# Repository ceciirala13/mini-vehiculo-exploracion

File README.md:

# mini-rover-lunar
Diseño prototipo de un mini rover lunar

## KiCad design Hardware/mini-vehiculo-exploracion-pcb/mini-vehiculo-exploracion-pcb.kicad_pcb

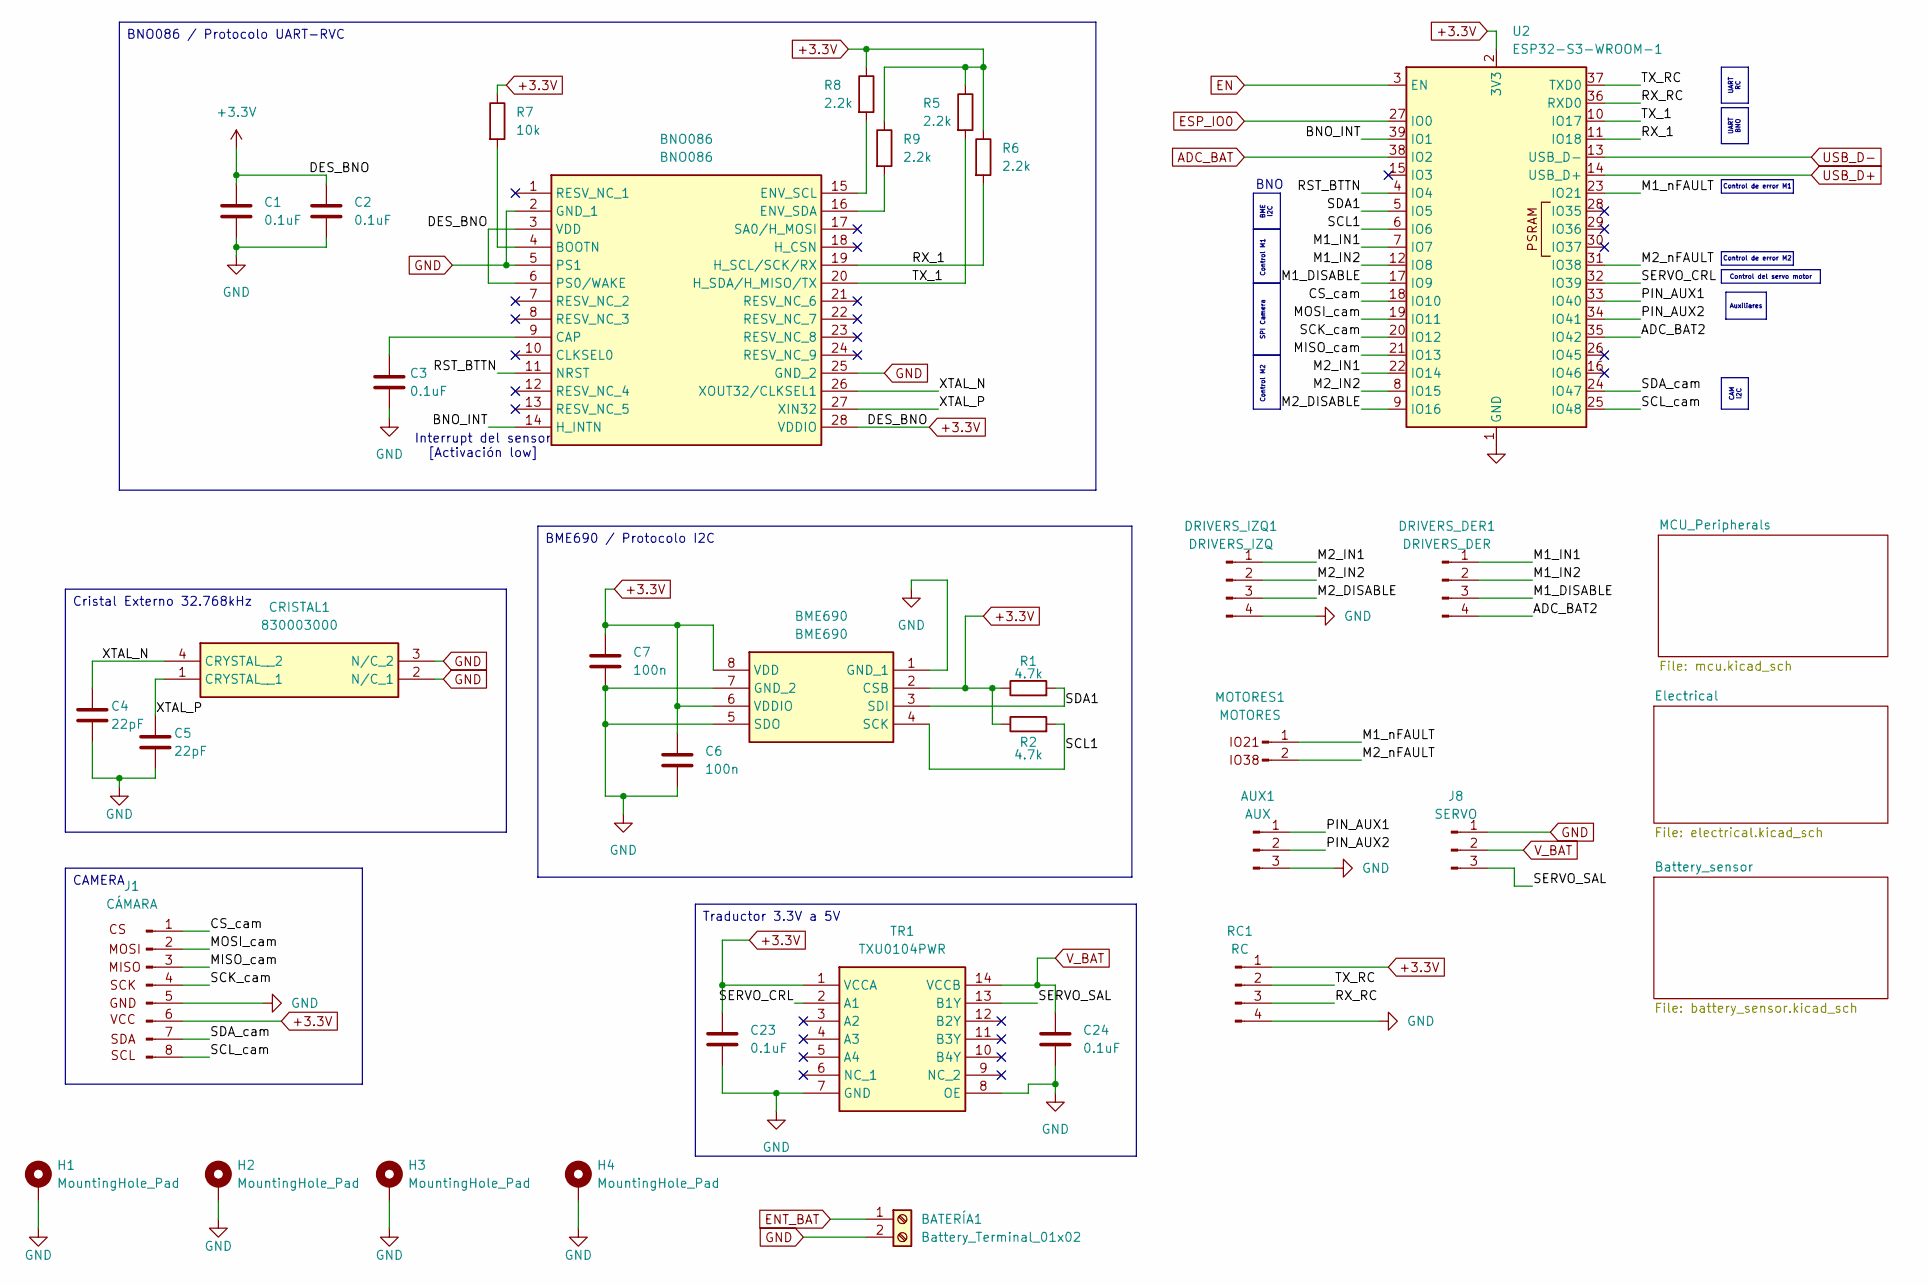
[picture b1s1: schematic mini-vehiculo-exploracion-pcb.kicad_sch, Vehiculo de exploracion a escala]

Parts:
AUX1: AUX; PinSocket_1x03_P2.54mm_Vertical
BATERÍA1: Battery_Terminal_01x02; TerminalBlock_Phoenix_MPT-0,5-2-2.54_1x02_P2.54mm_Horizontal
BME690: BME690; Mouser Part Number 262-BME690
BNO086: BNO086; Mouser Part Number 526-BNO086
C1, C2, C3, C23, C24: 0.1uF; C_0805_2012Metric_Pad1.18x1.45mm_HandSolder
C4, C5: 22pF; C_0805_2012Metric_Pad1.18x1.45mm_HandSolder
C6, C7: 100n; C_0805_2012Metric_Pad1.18x1.45mm_HandSolder
CRISTAL1: 830003000; Mouser Part Number 710-830003000
DRIVERS_DER1: DRIVERS_DER; PinSocket_1x04_P2.54mm_Vertical
DRIVERS_IZQ1: DRIVERS_IZQ; PinSocket_1x04_P2.54mm_Vertical
H1, H2, H3, H4: MountingHole_Pad; MountingHole_3.2mm_M3_Pad_Via
J1: CÁMARA; ArducamMINIOV2640
J8: SERVO; PinSocket_1x03_P2.54mm_Vertical
MOTORES1: MOTORES; PinSocket_1x02_P2.54mm_Vertical
R1, R2: 4.7k; R_0805_2012Metric_Pad1.20x1.40mm_HandSolder
R5, R6, R8, R9: 2.2k; R_0805_2012Metric_Pad1.20x1.40mm_HandSolder
R7: 10k; R_0805_2012Metric_Pad1.20x1.40mm_HandSolder
RC1: RC; PinSocket_1x04_P2.54mm_Vertical
TR1: TXU0104PWR; SOP65P640X120-14N; Mouser Part Number 595-TXU0104PWR
U2: ESP32-S3-WROOM-1; ESP32-S3-WROOM-1-P3JLC

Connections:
+3.3V: BME690.2 (CSB), BME690.6 (VDDIO), BME690.8 (VDD), BNO086.3 (VDD), BNO086.6 (PS0/WAKE), BNO086.28 (VDDIO), C1.1, C2.1, C6.1, C7.1, C23.1, J1.6 (VCC), R1.1, R2.1, R5.1, R6.1, R7.1, R8.1, R9.1, RC1.1, TR1.1 (VCCA), U2.2 (3V3); also elsewhere on the board
/BNO_INT: BNO086.14 (H_INTN), U2.39 (IO1); also elsewhere on the board
/CS_cam: J1.1 (CS), U2.18 (IO10); also elsewhere on the board
/M1_nFAULT: MOTORES1.1, U2.23 (IO21); also elsewhere on the board
/M2_nFAULT: MOTORES1.2, U2.31 (IO38); also elsewhere on the board
/MISO_cam: J1.3 (MISO), U2.21 (IO13); also elsewhere on the board
/MOSI_cam: J1.2 (MOSI), U2.19 (IO11); also elsewhere on the board
/PIN_AUX1: AUX1.1, U2.33 (IO40); also elsewhere on the board
/PIN_AUX2: AUX1.2, U2.34 (IO41); also elsewhere on the board
/RST_BTTN: BNO086.11 (NRST), U2.4 (IO4); also elsewhere on the board
/RX_1: BNO086.19 (H_SCL/SCK/RX), R6.2, U2.11 (IO18); also elsewhere on the board
/RX_RC: RC1.3, U2.36 (RXD0); also elsewhere on the board
/SCK_cam: J1.4 (SCK), U2.20 (IO12); also elsewhere on the board
/SCL1: BME690.4 (SCK), R2.2, U2.6 (IO6); also elsewhere on the board
/SCL_cam: J1.8 (SCL), U2.25 (IO48); also elsewhere on the board
/SDA1: BME690.3 (SDI), R1.2, U2.5 (IO5); also elsewhere on the board
/SDA_cam: J1.7 (SDA), U2.24 (IO47); also elsewhere on the board
/SERVO_CRL: TR1.2 (A1), U2.32 (IO39); also elsewhere on the board
/SERVO_SAL: J8.3, TR1.13 (B1Y)
/TX_1: BNO086.20 (H_SDA/H_MISO/TX), R5.2, U2.10 (IO17); also elsewhere on the board
/TX_RC: RC1.2, U2.37 (TXD0); also elsewhere on the board
/XTAL_N: BNO086.26 (XOUT32/CLKSEL1), C4.1, CRISTAL1.4 (CRYSTAL__2)
/XTAL_P: BNO086.27 (XIN32), C5.1, CRISTAL1.1 (CRYSTAL__1)
ENT_BAT: BATERÍA1.1; also elsewhere on the board
GND: AUX1.3, BATERÍA1.2, BME690.1 (GND_1), BME690.5 (SDO), BME690.7 (GND_2), BNO086.2 (GND_1), BNO086.5 (PS1), BNO086.25 (GND_2), C1.2, C2.2, C3.2, C4.2, C5.2, C6.2, C7.2, C23.2, C24.2, CRISTAL1.2 (N/C_1), CRISTAL1.3 (N/C_2), DRIVERS_IZQ1.4, H1.1, H2.1, H3.1, H4.1, J1.5 (GND), J8.1, RC1.4, TR1.7 (GND), TR1.8 (OE), U2.1 (GND), U2.40 (GND), U2.41 (GND); also elsewhere on the board
unnamed: BNO086.4 (BOOTN), R7.2
unnamed: BNO086.9 (CAP), C3.1
unnamed: BNO086.15 (ENV_SCL), R8.2
unnamed: BNO086.16 (ENV_SDA), R9.2
unnamed: DRIVERS_DER1.1, U2.7 (IO7)
unnamed: DRIVERS_DER1.2, U2.12 (IO8)
unnamed: DRIVERS_DER1.3, U2.17 (IO9)
unnamed: DRIVERS_DER1.4, U2.35 (IO42)
unnamed: DRIVERS_IZQ1.1, U2.22 (IO14)
unnamed: DRIVERS_IZQ1.2, U2.8 (IO15)
unnamed: DRIVERS_IZQ1.3, U2.9 (IO16)
V_BAT: C24.1, J8.2, TR1.14 (VCCB); also elsewhere on the board

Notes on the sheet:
Control de error M2
BNO
Control de error M1
Interrupt del sensor [Activación low]
CAMERA
UART BNO
BME690 / Protocolo I2C
Control del servo motor
UART RC
BME I2C
Control M2
Control M1
Cristal Externo 32.768kHz
SPI Camera
Traductor 3.3V a 5V
CAM I2C
BNO086 / Protocolo UART-RVC
Auxiliares

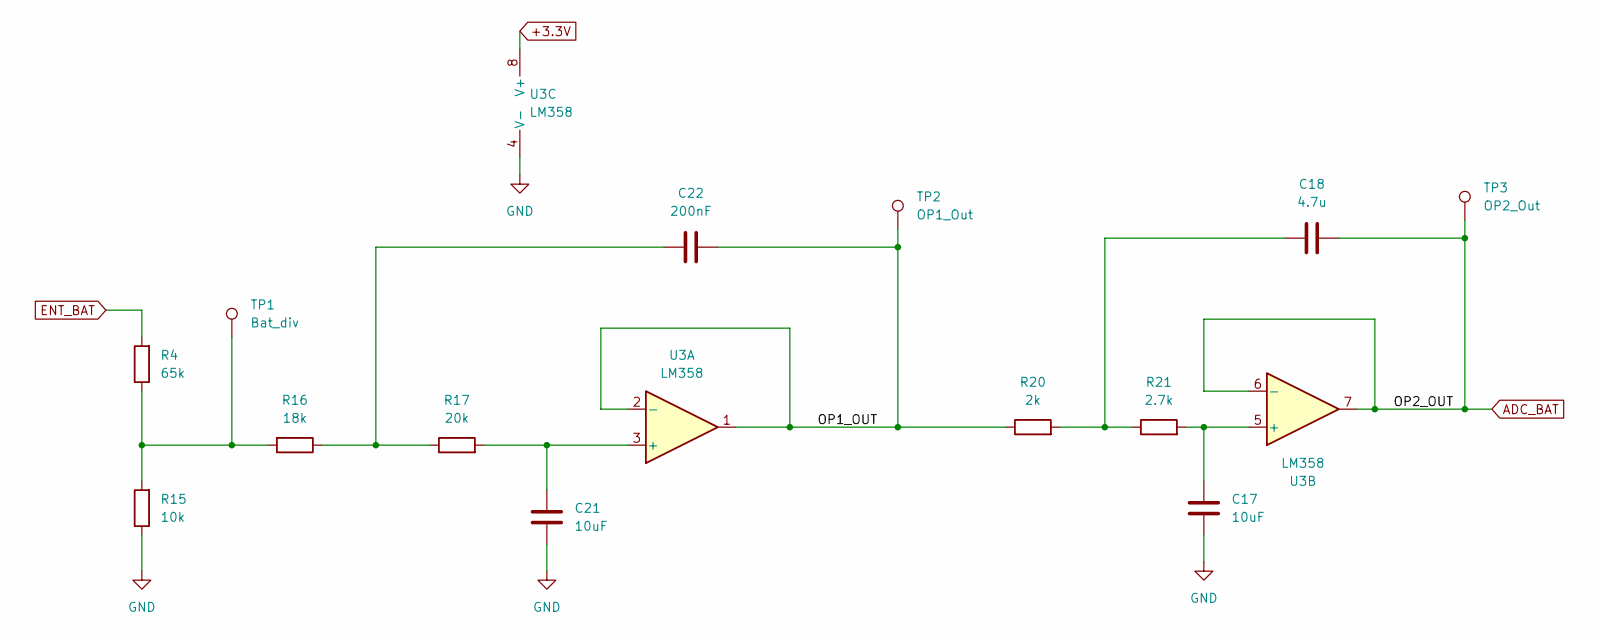
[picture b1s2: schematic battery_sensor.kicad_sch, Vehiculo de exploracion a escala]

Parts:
C17, C21: 10uF; C_0805_2012Metric_Pad1.18x1.45mm_HandSolder
C18: 4.7u; C_0805_2012Metric_Pad1.18x1.45mm_HandSolder
C22: 200nF; C_0805_2012Metric_Pad1.18x1.45mm_HandSolder
R4: 65k; R_0805_2012Metric_Pad1.20x1.40mm_HandSolder
R15: 10k; R_0805_2012Metric_Pad1.20x1.40mm_HandSolder
R16: 18k; R_0805_2012Metric_Pad1.20x1.40mm_HandSolder
R17: 20k; R_0805_2012Metric_Pad1.20x1.40mm_HandSolder
R20: 2k; R_0805_2012Metric_Pad1.20x1.40mm_HandSolder
R21: 2.7k; R_0805_2012Metric_Pad1.20x1.40mm_HandSolder
TP1: Bat_div; TestPoint_Pad_1.5x1.5mm
TP2: OP1_Out; TestPoint_Pad_1.5x1.5mm
TP3: OP2_Out; TestPoint_Pad_1.5x1.5mm
U3: LM358; DIP794W53P254L959H508Q8N

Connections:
+3.3V: U3.8 (V+); also elsewhere on the board
/Battery_sensor/OP1_OUT: C22.2, R20.1, TP2.1, U3.1, U3.2 (-)
ADC_BAT: C18.2, TP3.1, U3.6 (-), U3.7; also elsewhere on the board
ENT_BAT: R4.2; also elsewhere on the board
GND: C17.2, C21.2, R15.1, U3.4 (V-); also elsewhere on the board
unnamed: C18.1, R20.2, R21.1
unnamed: C22.1, R16.1, R17.1
unnamed: R4.1, R15.2, R16.2, TP1.1
unnamed: C21.1, R17.2, U3.3 (+)
unnamed: C17.1, R21.2, U3.5 (+)

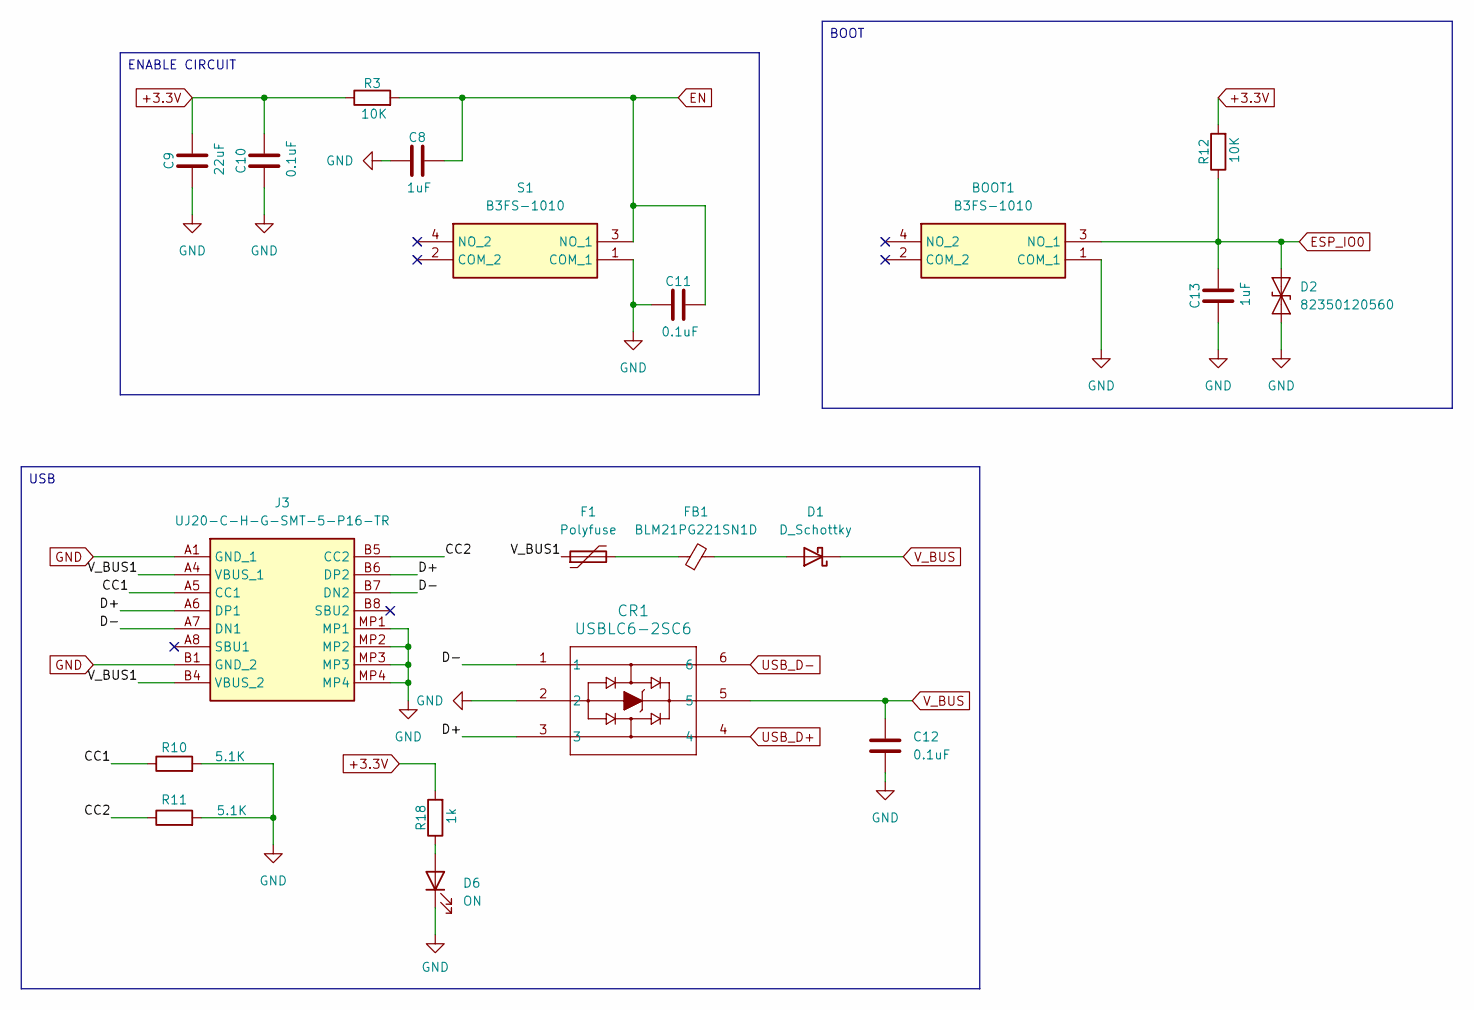
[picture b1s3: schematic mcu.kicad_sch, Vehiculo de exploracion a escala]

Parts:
BOOT1: B3FS-1010; B3FS-1000P; Mouser Part Number 653-B3FS-1010
C8, C13: 1uF; C_0805_2012Metric_Pad1.18x1.45mm_HandSolder
C9: 22uF; C_0805_2012Metric_Pad1.18x1.45mm_HandSolder
C10, C11, C12: 0.1uF; C_0805_2012Metric_Pad1.18x1.45mm_HandSolder
CR1: USBLC6-2SC6; SOT23-6L_STM
D1: D_Schottky; SD1206_AVX
D2: 82350120560; CR_50120560_WRE-M
D6: ON; LED_0805_2012Metric
F1: Polyfuse; C1_BEL
FB1: BLM21PG221SN1D; IND_BLM21_MUR
J3: UJ20-C-H-G-SMT-5-P16-TR; UJ20CHGSMT5P16TR; Mouser Part Number 179-UJ20CHGSMT5P16TR
R3, R12: 10K; R_0805_2012Metric_Pad1.20x1.40mm_HandSolder
R10, R11: 5.1K; R_0805_2012Metric_Pad1.20x1.40mm_HandSolder
R18: 1k; R_0805_2012Metric_Pad1.20x1.40mm_HandSolder
S1: B3FS-1010; B3FS-1000P; Mouser Part Number 653-B3FS-1010

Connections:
+3.3V: C9.2, C10.2, R3.1, R12.2, R18.2; also elsewhere on the board
/MCU_Peripherals/CC1: J3.A5 (CC1), R10.1
/MCU_Peripherals/CC2: J3.B5 (CC2), R11.1
/MCU_Peripherals/D+: CR1.3, J3.A6 (DP1), J3.B6 (DP2)
/MCU_Peripherals/D-: CR1.1, J3.A7 (DN1), J3.B7 (DN2)
/MCU_Peripherals/V_BUS1: F1.1, J3.A4 (VBUS_1), J3.B4 (VBUS_2)
EN: C8.2, C11.2, R3.2, S1.3 (NO_1); also elsewhere on the board
ESP_IO0: BOOT1.3 (NO_1), C13.2, D2.2 (A2), R12.1; also elsewhere on the board
GND: BOOT1.1 (COM_1), C8.1, C9.1, C10.1, C11.1, C12.2, C13.1, CR1.2, D2.1 (A1), D6.1 (K), J3.A1 (GND_1), J3.B1 (GND_2), J3.MP1, J3.MP2, J3.MP3, J3.MP4, R10.2, R11.2, S1.1 (COM_1); also elsewhere on the board
unnamed: D1.2 (A), FB1.2
unnamed: D6.2 (A), R18.1
unnamed: F1.2, FB1.1
USB_D+: CR1.4; also elsewhere on the board
USB_D-: CR1.6; also elsewhere on the board
V_BUS: C12.1, CR1.5, D1.1 (K); also elsewhere on the board

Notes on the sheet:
BOOT
USB
ENABLE CIRCUIT

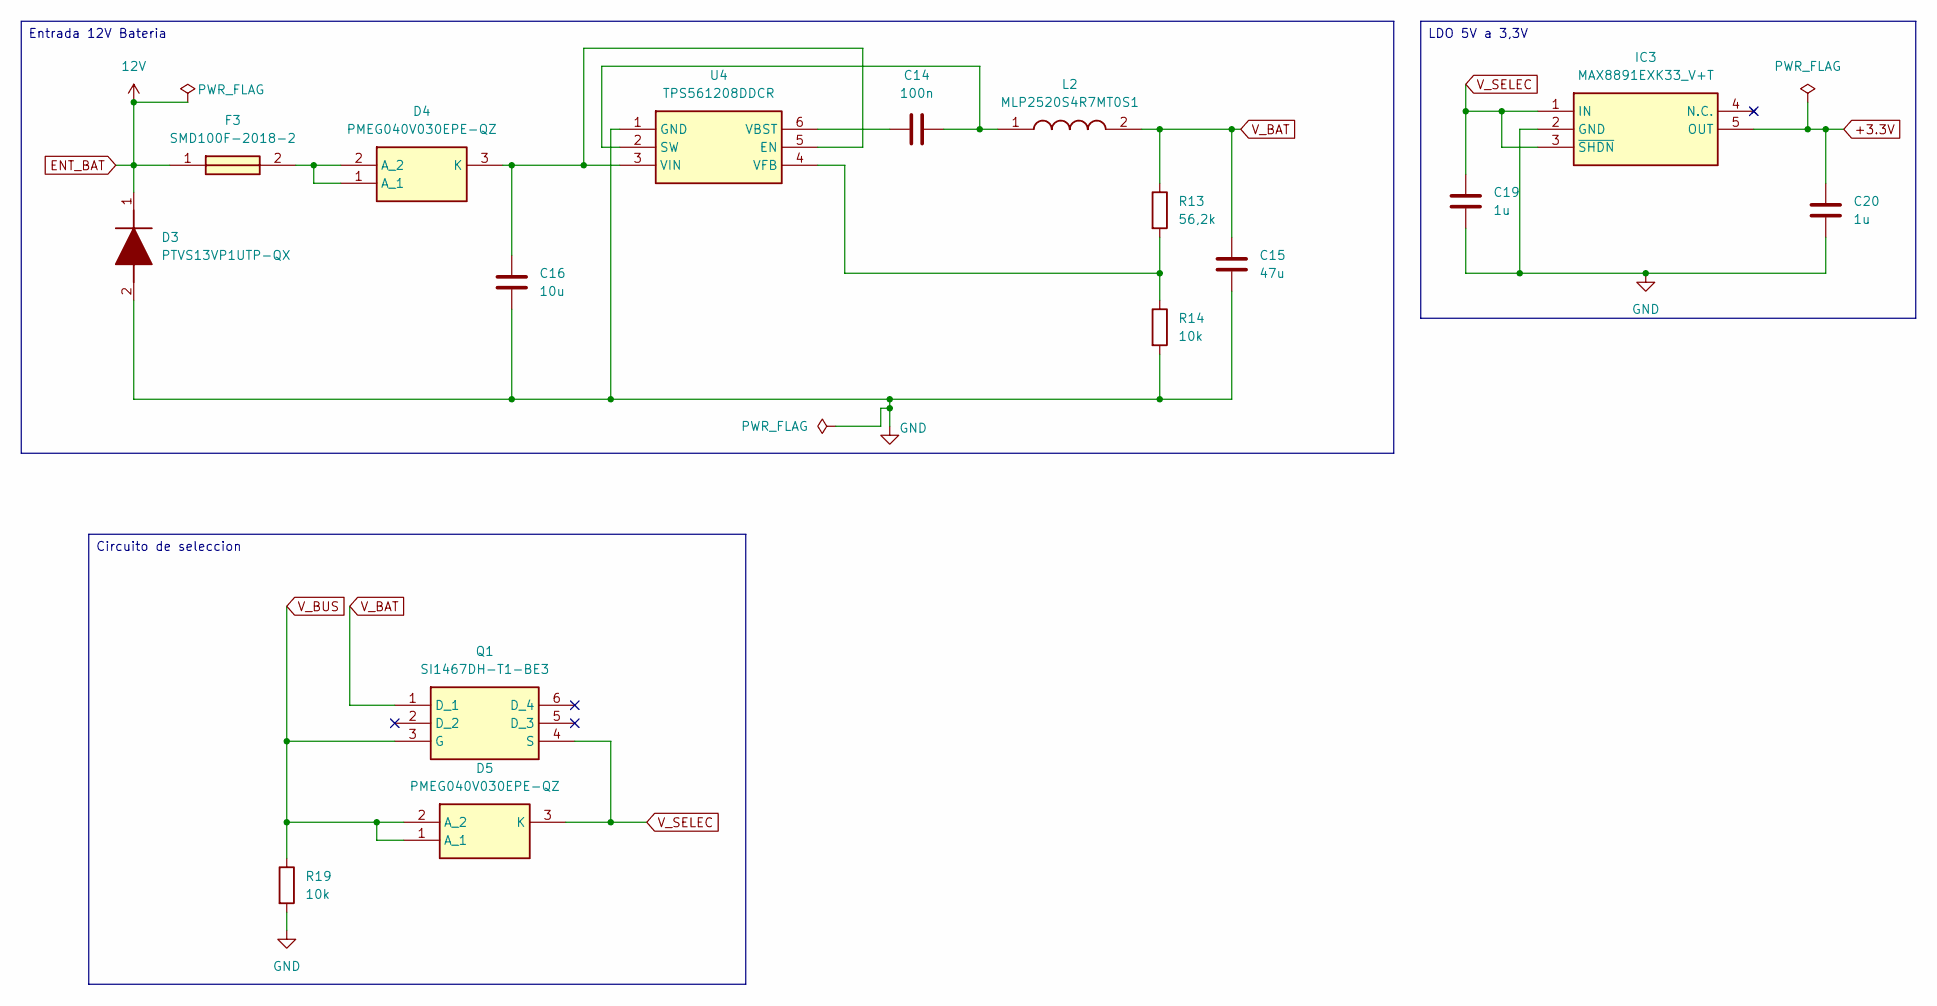
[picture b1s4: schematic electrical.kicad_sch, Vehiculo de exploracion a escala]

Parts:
C14: 100n; C_0805_2012Metric_Pad1.18x1.45mm_HandSolder
C15: 47u; C_0805_2012Metric_Pad1.18x1.45mm_HandSolder
C16: 10u; C_0805_2012Metric_Pad1.18x1.45mm_HandSolder
C19, C20: 1u; C_0805_2012Metric_Pad1.18x1.45mm_HandSolder
D3: PTVS13VP1UTP-QX; SODFL4725X110N; Manufacturer_Part_Number PTVS13VP1UTP-QX
D4, D5: PMEG040V030EPE-QZ; PMEG040V030EPEQZ; Mouser Part Number 771-PMEG040V030EPEQZ
F3: SMD100F-2018-2; SMD030F20182; Mouser Part Number 650-SMD100F-2018-2
IC3: MAX8891EXK33_V+T; SOT65P210X110-5N; Manufacturer_Part_Number MAX8891EXK33/V+T
L2: MLP2520S4R7MT0S1; INDC2520X100N; Mouser Part Number 810-MLP2520S4R7MT0S1
Q1: SI1467DH-T1-BE3; SOT65P210X110-6N; Mouser Part Number 78-SI1467DH-T1-BE3
R13: 56,2k; R_0805_2012Metric_Pad1.20x1.40mm_HandSolder
R14, R19: 10k; R_0805_2012Metric_Pad1.20x1.40mm_HandSolder
U4: TPS561208DDCR; SOT95P280X110-6N; Mouser Part Number 595-TPS561208DDCR

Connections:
+3.3V: C20.1, IC3.5 (OUT); also elsewhere on the board
ENT_BAT: D3.1 (K), F3.1; also elsewhere on the board
GND: C15.2, C16.2, C19.2, C20.2, D3.2 (A), IC3.2 (GND), R14.2, R19.2, U4.1 (GND); also elsewhere on the board
unnamed: D4.1 (A_1), D4.2 (A_2), F3.2
unnamed: C16.1, D4.3 (K), U4.3 (VIN), U4.5 (EN)
unnamed: C14.2, L2.1, U4.2 (SW)
unnamed: C14.1, U4.6 (VBST)
unnamed: R13.2, R14.1, U4.4 (VFB)
V_BAT: C15.1, L2.2, Q1.1 (D_1), R13.1; also elsewhere on the board
V_BUS: D5.1 (A_1), D5.2 (A_2), Q1.3 (G), R19.1; also elsewhere on the board
V_SELEC: C19.1, D5.3 (K), IC3.1 (IN), IC3.3 (~SHDN), Q1.4 (S)

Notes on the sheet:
Entrada 12V Bateria
LDO 5V a 3,3V
Circuito de seleccion

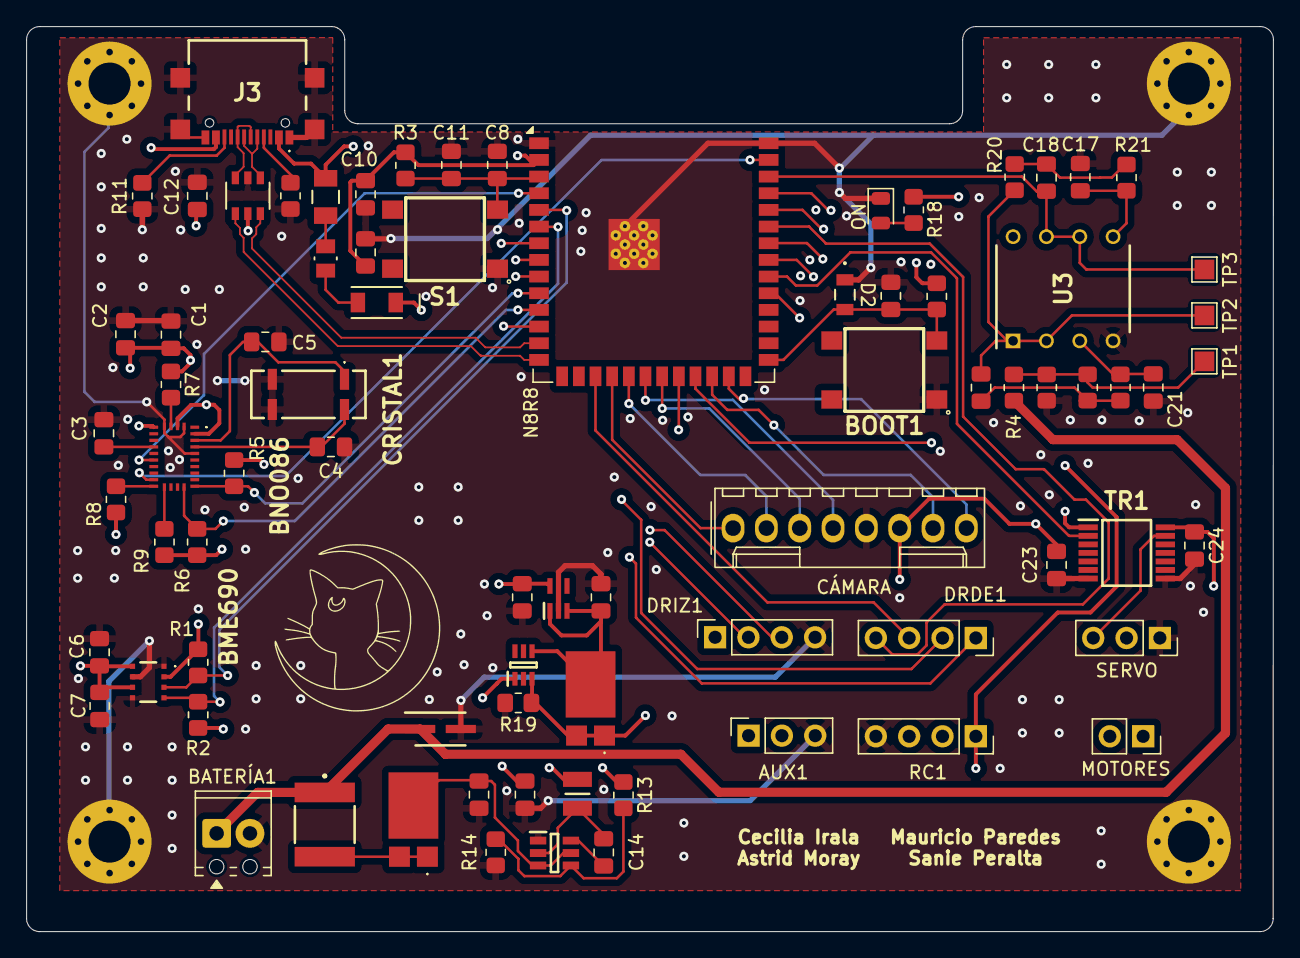
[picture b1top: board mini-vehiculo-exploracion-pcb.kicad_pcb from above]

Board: 4 copper layers, 95.0 x 69.0 mm, 83 parts (0 on the bottom side), 63 nets.

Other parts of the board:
DRDE1: DRIVERS_DER; PinSocket_1x04_P2.54mm_Vertical
DRIZ1: DRIVERS_IZQ; PinSocket_1x04_P2.54mm_Vertical
N8R8: ESP32-S3-WROOM-1; ESP32-S3-WROOM-1-P3JLC

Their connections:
+3.3V: N8R8.2 (3V3); also elsewhere on the board
/ADC_BAT2: DRDE1.4, N8R8.35 (IO42)
/BNO_INT: N8R8.39 (IO1); also elsewhere on the board
/CS_cam: N8R8.18 (IO10); also elsewhere on the board
/M1_DISABLE: DRDE1.3, N8R8.17 (IO9)
/M1_IN1: DRDE1.1, N8R8.7 (IO7)
/M1_IN2: DRDE1.2, N8R8.12 (IO8)
/M1_nFAULT: N8R8.23 (IO21); also elsewhere on the board
/M2_DISABLE: DRIZ1.3, N8R8.9 (IO16)
/M2_IN1: DRIZ1.1, N8R8.22 (IO14)
/M2_IN2: DRIZ1.2, N8R8.8 (IO15)
/M2_nFAULT: N8R8.31 (IO38); also elsewhere on the board
/MISO_cam: N8R8.21 (IO13); also elsewhere on the board
/MOSI_cam: N8R8.19 (IO11); also elsewhere on the board
/PIN_AUX1: N8R8.33 (IO40); also elsewhere on the board
/PIN_AUX2: N8R8.34 (IO41); also elsewhere on the board
/RST_BTTN: N8R8.4 (IO4); also elsewhere on the board
/RX_1: N8R8.11 (IO18); also elsewhere on the board
/RX_RC: N8R8.36 (RXD0); also elsewhere on the board
/SCK_cam: N8R8.20 (IO12); also elsewhere on the board
/SCL1: N8R8.6 (IO6); also elsewhere on the board
/SCL_cam: N8R8.25 (IO48); also elsewhere on the board
/SDA1: N8R8.5 (IO5); also elsewhere on the board
/SDA_cam: N8R8.24 (IO47); also elsewhere on the board
/SERVO_CRL: N8R8.32 (IO39); also elsewhere on the board
/TX_1: N8R8.10 (IO17); also elsewhere on the board
/TX_RC: N8R8.37 (TXD0); also elsewhere on the board
ADC_BAT: N8R8.38 (IO2); also elsewhere on the board
EN: N8R8.3 (EN); also elsewhere on the board
ESP_IO0: N8R8.27 (IO0); also elsewhere on the board
GND: DRIZ1.4, N8R8.1 (GND), N8R8.40 (GND), N8R8.41 (GND); also elsewhere on the board
USB_D+: N8R8.14 (USB_D+); also elsewhere on the board
USB_D-: N8R8.13 (USB_D-); also elsewhere on the board

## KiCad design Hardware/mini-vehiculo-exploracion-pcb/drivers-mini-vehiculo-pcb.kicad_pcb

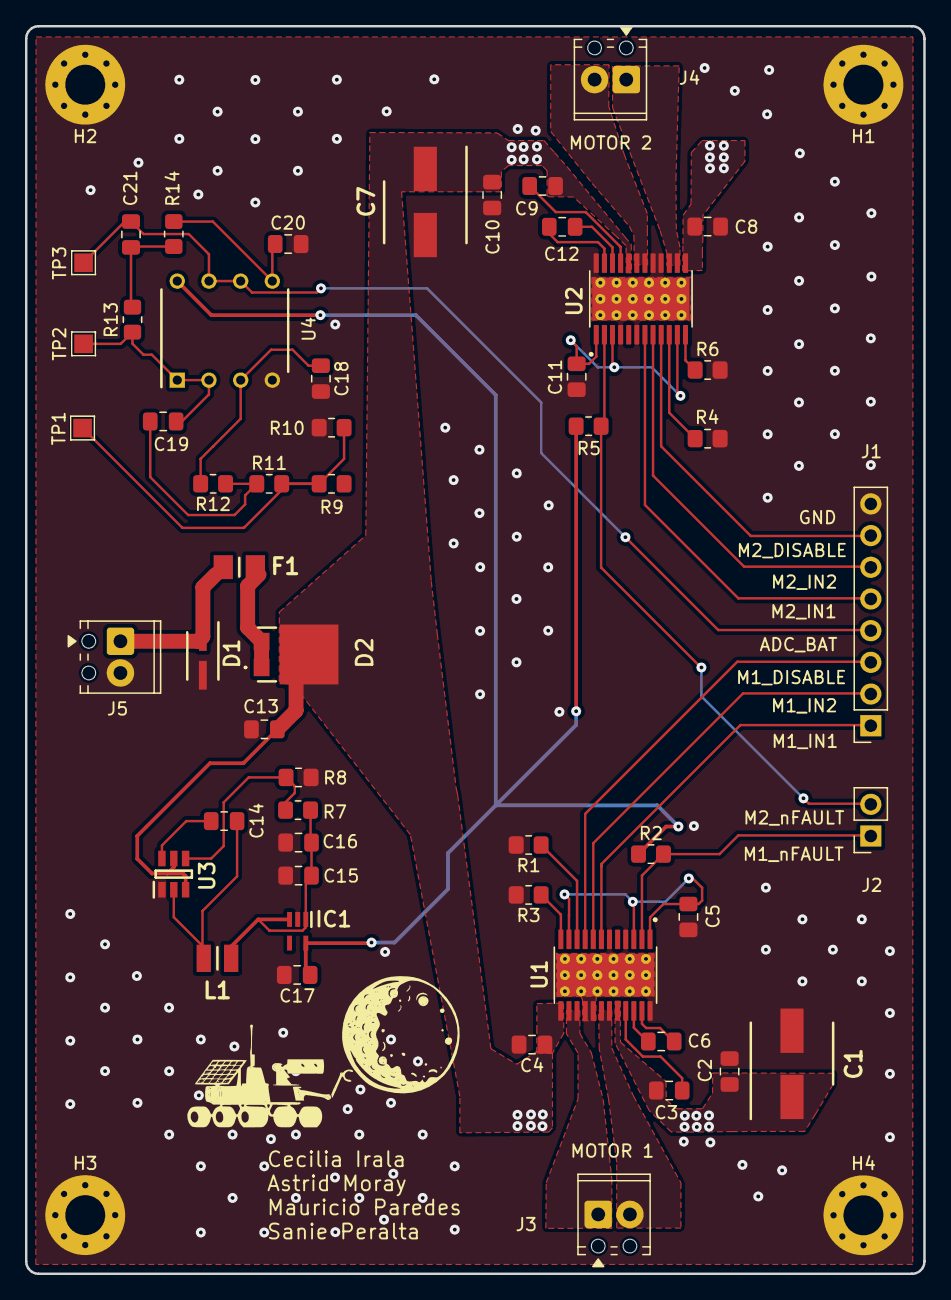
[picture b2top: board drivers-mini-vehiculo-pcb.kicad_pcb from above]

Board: 2 copper layers, 72.0 x 100.0 mm, 56 parts (0 on the bottom side), 40 nets.

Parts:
C1, C7: 180u; CAPAE660X610N
C2, C4, C8, C10: 0.1u; C_0805_2012Metric_Pad1.18x1.45mm_HandSolder
C3, C5, C9, C11, C16, C17: 1u; C_0805_2012Metric_Pad1.18x1.45mm_HandSolder
C6, C12: 47n; C_0805_2012Metric_Pad1.18x1.45mm_HandSolder
C13: 10u; C_0805_2012Metric_Pad1.18x1.45mm_HandSolder
C14: 100n; C_0805_2012Metric_Pad1.18x1.45mm_HandSolder
C15: 47u; C_0805_2012Metric_Pad1.18x1.45mm_HandSolder
C18, C20: 10uF; C_0805_2012Metric_Pad1.18x1.45mm_HandSolder
C19: 200nF; C_0805_2012Metric_Pad1.18x1.45mm_HandSolder
C21: 4.7u; C_0805_2012Metric_Pad1.18x1.45mm_HandSolder
D1: PTVS13VP1UTP-QX; SODFL4725X110N
D2: V15PM6HM3_H; V15PM6HM3H
F1: SF-1206SA1500W-2; FUSC3217X123N
H1, H2, H3, H4: MountingHole_Pad; MountingHole_3.2mm_M3_Pad_Via
IC1: MAX8891EXK33_V+T; SOT65P210X110-5N
J1: Conn_01x08_Pin_drv; PinSocket_1x08_P2.54mm_Vertical
J2: Conn_01x02_Pin_drv; PinSocket_1x02_P2.54mm_Vertical
J4: Motor1_Terminal; TerminalBlock_Phoenix_MPT-0,5-2-2.54_1x02_P2.54mm_Horizontal
J4#2: Motor2_Terminal; TerminalBlock_Phoenix_MPT-0,5-2-2.54_1x02_P2.54mm_Horizontal
J5: Battery_Terminal_01x02; TerminalBlock_Phoenix_MPT-0,5-2-2.54_1x02_P2.54mm_Horizontal
L1: MLP2520S4R7MT0S1; INDC2520X100N
R1, R3, R4, R6: 820; R_0805_2012Metric_Pad1.20x1.40mm_HandSolder
R2, R5, R8, R10: 10k; R_0805_2012Metric_Pad1.20x1.40mm_HandSolder
R7: 56,2k; R_0805_2012Metric_Pad1.20x1.40mm_HandSolder
R9: 65k; R_0805_2012Metric_Pad1.20x1.40mm_HandSolder
R11: 18k; R_0805_2012Metric_Pad1.20x1.40mm_HandSolder
R12: 20k; R_0805_2012Metric_Pad1.20x1.40mm_HandSolder
R13: 2k; R_0805_2012Metric_Pad1.20x1.40mm_HandSolder
R14: 2.7k; R_0805_2012Metric_Pad1.20x1.40mm_HandSolder
TP1: Bat_div; TestPoint_Pad_1.5x1.5mm
TP2: OP1_Out; TestPoint_Pad_1.5x1.5mm
TP3: OP2_Out; TestPoint_Pad_1.5x1.5mm
U1, U2: DRV8873HPWPRQ1; SOP65P640X120-25N
U3: TPS561208DDCR; SOT95P280X110-6N
U4: LM358; DIP794W53P254L959H508Q8N

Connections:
+3.3V: C17.1, IC1.5 (OUT), R2.1, R5.1, U4.8 (V+)
+5V: C15.1, C16.1, IC1.1 (IN), IC1.3 (~SHDN), L1.2, R7.1
+12V: C1.1, C2.1, C3.2, C4.1, C7.1, C8.1, C9.2, C10.1, C13.1, D2.3 (K), U1.13 (VM), U1.20 (VM), U2.13 (VM), U2.20 (VM), U3.3 (VIN), U3.5 (EN)
/Battery Sensor/OP1_OUT: C19.2, R13.1, TP2.1, U4.1, U4.2 (-)
/CPH1: C6.1, U1.22 (CPH)
/CPH2: C12.1, U2.22 (CPH)
/CPL1: C6.2, U1.23 (CPL)
/CPL2: C12.2, U2.23 (CPL)
/IPROPI1_1: R1.1, U1.10 (IPROPI1)
/IPROPI1_2: R4.1, U2.10 (IPROPI1)
/IPROPI2_1: R3.1, U1.12 (IPROPI2)
/IPROPI2_2: R6.1, U2.12 (IPROPI2)
/M1_DISABLE: J1.3, U1.9 (DISABLE)
/M1_IN1: J1.1, U1.7 (EN/IN1)
/M1_IN2: J1.2, U1.8 (PH/IN2)
/M1_V+: J4.2, U1.18 (OUT1), U1.19 (OUT1)
/M1_V-: J4.1, U1.14 (OUT2), U1.15 (OUT2)
/M1_nFAULT: J2.1, R2.2, U1.2 (NFAULT)
/M2_DISABLE: J1.7, U2.9 (DISABLE)
/M2_IN1: J1.5, U2.7 (EN/IN1)
/M2_IN2: J1.6, U2.8 (PH/IN2)
/M2_V+: J4#2.2, U2.18 (OUT1), U2.19 (OUT1)
/M2_V-: J4#2.1, U2.14 (OUT2), U2.15 (OUT2)
/M2_nFAULT: J2.2, R5.2, U2.2 (NFAULT)
/VCP1: C3.1, U1.21 (VCP)
/VCP2: C9.1, U2.21 (VCP)
ADC_BAT: C21.2, J1.4, TP3.1, U4.6 (-), U4.7
DVDD_1: C5.1, U1.1 (DVDD), U1.3 (MODE), U1.11 (NSLEEP)
DVDD_2: C11.1, U2.1 (DVDD), U2.3 (MODE), U2.11 (NSLEEP)
GND: C1.2, C2.2, C4.2, C5.2, C7.2, C8.2, C10.2, C11.2, C13.2, C15.2, C16.2, C17.2, C18.2, C20.2, D1.2 (A), H1.1, H2.1, H3.1, H4.1, IC1.2 (GND), J1.8, J5.2, R1.2, R3.2, R4.2, R6.2, R8.2, R10.1, U1.4 (SR), U1.6 (NOL), U1.16 (SRC), U1.17 (SRC), U1.24 (GND), U1.25 (EXP), U1.P1 (EXP), U1.P2 (EXP), U1.P3 (EXP), U1.P4 (EXP), U1.P5 (EXP), U1.P6 (EXP), U1.P7 (EXP), U1.P8 (EXP), U1.P9 (EXP), U1.P10 (EXP), U1.P11 (EXP), U1.P12 (EXP), U1.P13 (EXP), U1.P14 (EXP), U1.P15 (EXP), U1.P16 (EXP), U1.P17 (EXP), U1.P18 (EXP), U2.4 (SR), U2.6 (NOL), U2.16 (SRC), U2.17 (SRC), U2.24 (GND), U2.25 (EXP), U2.P1 (EXP), U2.P2 (EXP), U2.P3 (EXP), U2.P4 (EXP), U2.P5 (EXP), U2.P6 (EXP), U2.P7 (EXP), U2.P8 (EXP), U2.P9 (EXP), U2.P10 (EXP), U2.P11 (EXP), U2.P12 (EXP), U2.P13 (EXP), U2.P14 (EXP), U2.P15 (EXP), U2.P16 (EXP), U2.P17 (EXP), U2.P18 (EXP), U3.1 (GND), U4.4 (V-)
unnamed: C19.1, R11.1, R12.1
unnamed: C21.1, R13.2, R14.1
unnamed: D2.1 (A_1), D2.2 (A_2), F1.2
unnamed: R9.1, R10.2, R11.2, TP1.1
unnamed: C14.2, L1.1, U3.2 (SW)
unnamed: C14.1, U3.6 (VBST)
unnamed: R7.2, R8.1, U3.4 (VFB)
unnamed: C18.1, R12.2, U4.3 (+)
unnamed: C20.1, R14.2, U4.5 (+)
V_BAT: D1.1 (K), F1.1, J5.1

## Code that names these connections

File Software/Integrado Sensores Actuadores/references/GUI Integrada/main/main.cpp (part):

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    constexpr uint32_t   UART_BAUD    = 921600;

    // Motor 1 (DRV8873-Q1 #1)
    constexpr gpio_num_t M1_IN1       = GPIO_NUM_7;
    constexpr gpio_num_t M1_IN2       = GPIO_NUM_4;
    constexpr gpio_num_t M1_NFAULT    = GPIO_NUM_21;
    constexpr gpio_num_t M1_DISABLE   = GPIO_NUM_9;
    constexpr gpio_num_t M1_NSLEEP    = GPIO_NUM_NC; // Configurado por Hardware (-1 / NC)

    // Motor 2 (DRV8873-Q1 #2)
    constexpr gpio_num_t M2_IN1       = GPIO_NUM_14;
    constexpr gpio_num_t M2_IN2       = GPIO_NUM_8;
    constexpr gpio_num_t M2_NFAULT    = GPIO_NUM_38;
    constexpr gpio_num_t M2_DISABLE   = GPIO_NUM_16;
    constexpr gpio_num_t M2_NSLEEP    = GPIO_NUM_NC; // Configurado por Hardware (-1 / NC)

    // Servomotor para Dirección
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
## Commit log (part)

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2026-02-09 Create componentes-electronicos
2026-02-14 Update componentes-electronicos
2026-02-14 Create Prototipos
2026-02-14 Create Librerias
2026-02-28 Create links
2026-02-28 Create ESP32
2026-02-28 Create ccc
2026-03-04 Add kicad file and ESP32 schematic
2026-03-04 Add BNO086 initial
2026-03-05 Adicion de los drivers para control de motores
2026-03-06 Add driver sym to assets
2026-03-06 Add arducam library
2026-03-06 Fixing labels
2026-03-06 add bme280
2026-03-07 Add BMP585 library
2026-03-07 Remove BMP585, Add BME690
2026-03-07 Carga de librerias de componentes para proteccion energetica
2026-03-07 continuacion de carga de librerias
2026-03-08 update bno086 schematic
2026-03-08 add separate driver schematic
2026-03-10 add bme690
2026-03-11 Pins for camera and drivers
2026-03-11 Add enable circuit and USB schematic v1
2026-03-11 Add n_FAULT pin, changed I2C pins for cam
2026-03-13 add driver pin labels
2026-03-13 Add USB protection
2026-03-13 Add componentes.xlsx
2026-03-13 Add boot to the schematic
2026-03-13 checking schematic/sheets
2026-03-13 cambios
2026-03-13 carga de librerias existentes a la carpeta assets
2026-03-13 carga de librerias de componentes adicionales
2026-03-13 add informe p3 - avance
2026-03-14 create driver-mini-vehiculo-pcb pcb
2026-03-14 update componentes
2026-03-14 Update capacitor values
2026-03-15 creacion electrical sheet
2026-03-15 implementacion buck 3,3V
2026-03-15 updated connectors for driver
2026-03-15 LDO 5V a 3,3V
2026-03-15 Carga librerias MOSFET corriente inversa
2026-03-16 add footprints
2026-03-16 Carga de librerias
2026-03-16 edicion parcial proteccion entrada
2026-03-16 continue informe
2026-03-16 cambio de componentes e implementacion circuito de seleccion
2026-03-17 carga librerias pcb de drivers
2026-03-17 reductores de voltaje drivers
2026-03-17 conclusion electrical drivers
2026-03-18 carga libreria Schottky 1
2026-03-18 cambio convertidor 3,3V a 5V
2026-03-18 actualizacion labels pcb de control
2026-03-18 actualizacion labels pcb drivers
2026-03-19 carga libreria schottky drivers
2026-03-19 reemplazo diodo schottky drivers
2026-03-20 Add pin headers, run ERC
2026-03-20 Assigned NET CLASSES
2026-03-20 Add battery sensor
2026-03-20 add capacitor footprints
2026-03-20 updated driver pcb
2026-03-20 updated resistor footprint
2026-03-20 algo
2026-03-20 carga librerias
2026-03-20 actualizacion fusible drivers
2026-03-20 updated pcb drv
2026-03-21 cambio circuito 5V pcb control
2026-03-21 carga libreria bobina
2026-03-21 changes etc
2026-03-21 updated sockets drv
2026-03-21 add lm358 library
2026-03-25 initiate pcb connections
2026-03-26 innit pcb
2026-03-26 Add netclassses, mounting holes and terminal block
2026-03-26 Update pcb from schematic
2026-03-27 fix bug pcb
2026-03-27 Revert "fix bug pcb"
    This reverts commit 95896929b2c40d1d86d6f174368d0f9d923b36b5.
2026-03-27 Revert "cambios"
    This reverts commit 18d6c077649d06db3e4be51193d20dbced0bef3d, reversing
    changes made to f53350afebab44693d0a4c4c217b64a1fc0c425b.
2026-03-27 continue pcb
2026-03-28 carga de huellas de conectores jst 3 a 7 pines
2026-03-28 change pcb1
2026-03-28 carga huellas jst 2 y 8 pines
2026-03-28 updated drv pcb
2026-03-28 change pcb2
2026-03-28 adicion de bornera pcb drivers y organizacion de entrada
2026-03-28 updated vm connection
2026-03-28 cambios rama de drivers
2026-03-28 carga modelos 3d jst
2026-03-28 update pcb3
2026-03-29 updated gnd and 12v zones
2026-03-29 updated gnd plane
2026-03-29 Reorder
2026-03-29 Changed to 4 layers
2026-03-29 Gerger file
2026-03-29 carga de modelos 3D componentes varios
2026-03-29 updated 3d models
2026-03-29 carga fusible faltante
2026-03-29 cambio de fusible
2026-03-29 update pcb4
2026-03-29 updated serigraphy
2026-03-29 finish pcb5
2026-03-29 updated srgphy
2026-03-29 Update 3d
2026-04-10 Update USB layout and changed stackup
2026-04-10 Clean
2026-04-10 Clean folder
2026-04-11 reduced vias quantity
2026-04-13 add vias
2026-04-13 innit fix edgecut
2026-04-14 fin adapt edgecuts
2026-04-14 finn
2026-04-14 Add gerber
2026-04-15 Changed 3v3 dist
2026-04-16 Add gnds
2026-04-17 added logo
2026-04-17 check pcb
2026-04-18 edit1
2026-04-20 add luna
2026-04-20 add fab files
2026-04-23 download gerber
2026-04-24 fab files pcb control
2026-04-24 update pcb control fab files
2026-04-25 new drill pcb
2026-04-25 cl pcb
2026-05-30 Carga de programacion para el BME690
2026-05-31 add libraries
